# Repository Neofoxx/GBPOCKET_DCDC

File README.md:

# Alternative DCDC converter board for the Gameboy Pocket

This board provides higher efficiency than the stock converter, alowwing you to use rechargeable bateries to their full potential.

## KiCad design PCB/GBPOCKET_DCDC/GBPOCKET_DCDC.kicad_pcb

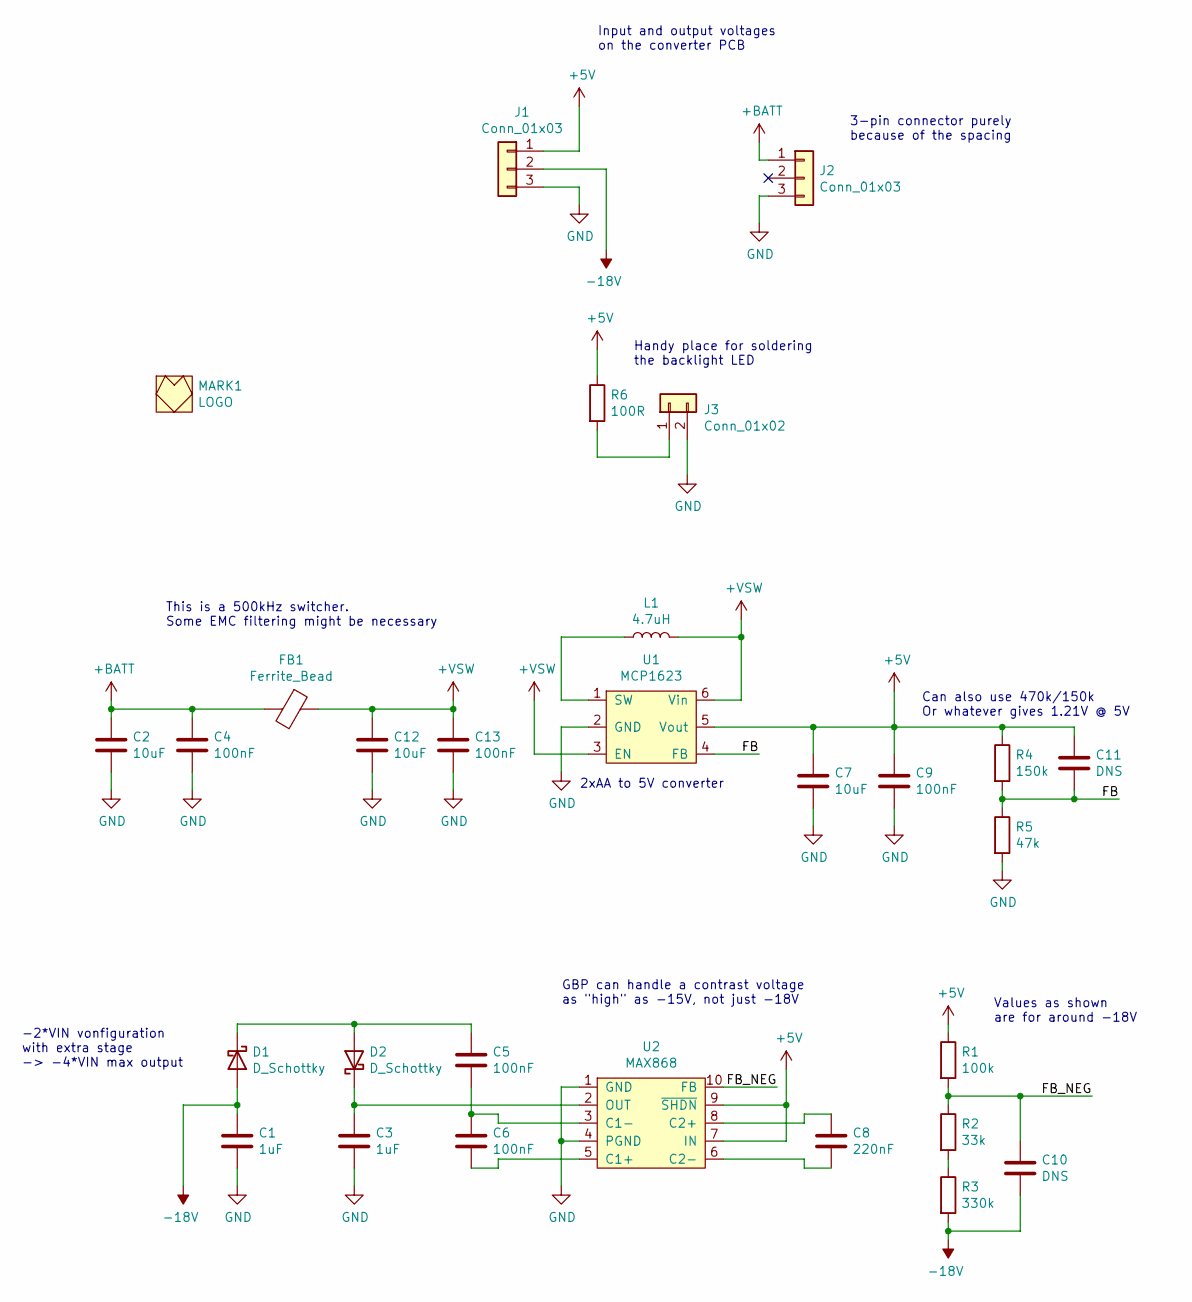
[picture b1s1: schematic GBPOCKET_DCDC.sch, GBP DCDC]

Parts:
C1, C3: 1uF; C_0603_1608Metric_Pad1.08x0.95mm_HandSolder
C2, C7, C12: 10uF; C_0805_2012Metric_Pad1.18x1.45mm_HandSolder
C4, C5, C6, C9, C13: 100nF; C_0603_1608Metric_Pad1.08x0.95mm_HandSolder
C8: 220nF; C_0603_1608Metric_Pad1.08x0.95mm_HandSolder
C10, C11: DNS; C_0603_1608Metric_Pad1.08x0.95mm_HandSolder
D1, D2: D_Schottky; D_SOD-323_HandSoldering
FB1: Ferrite_Bead; L_0805_2012Metric_Pad1.15x1.40mm_HandSolder
J1, J2: Conn_01x03; PinHeader_1x03_P2.54mm_Vertical
J3: Conn_01x02; PinHeader_1x02_P2.54mm_Vertical
L1: 4.7uH; SMNR4018_(1616FPS)
MARK1: LOGO; FOX_LOGO_SILK
R1: 100k; R_0603_1608Metric_Pad0.98x0.95mm_HandSolder
R2: 33k; R_0603_1608Metric_Pad0.98x0.95mm_HandSolder
R3: 330k; R_0603_1608Metric_Pad0.98x0.95mm_HandSolder
R4: 150k; R_0603_1608Metric_Pad0.98x0.95mm_HandSolder
R5: 47k; R_0603_1608Metric_Pad0.98x0.95mm_HandSolder
R6: 100R; R_0603_1608Metric_Pad0.98x0.95mm_HandSolder
U1: MCP1623; SOT-23-6_Handsoldering
U2: MAX868; MSOP-10_3x3mm_P0.5mm

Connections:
+5V: C7.1, C9.1, C11.1, J1.1, R1.1, R4.1, R6.1, U1.5 (Vout), U2.7 (IN), U2.9 (~SHDN~)
+BATT: C2.1, C4.1, FB1.2, J2.1
+VSW: C12.1, C13.1, FB1.1, L1.2, U1.3 (EN), U1.6 (Vin)
-18V: C1.1, C10.2, D1.2 (A), J1.2, R3.2
/FB: C11.2, R4.2, R5.1, U1.4 (FB)
/FB_NEG: C10.1, R1.2, R2.1, U2.10 (FB)
GND: C1.2, C2.2, C3.2, C4.2, C7.2, C9.2, C12.2, C13.2, J1.3, J2.3, J3.2, R5.2, U1.2 (GND), U2.1 (GND), U2.4 (PGND)
unnamed: C3.1, D2.1 (K), U2.2 (OUT)
unnamed: C5.1, D1.1 (K), D2.2 (A)
unnamed: C5.2, C6.1, U2.3 (C1-)
unnamed: C6.2, U2.5 (C1+)
unnamed: C8.1, U2.8 (C2+)
unnamed: C8.2, U2.6 (C2-)
unnamed: J3.1, R6.2
unnamed: L1.1, U1.1 (SW)
unnamed: R2.2, R3.1

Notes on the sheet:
Input and output voltages on the converter PCB
3-pin connector purely because of the spacing
This is a 500kHz switcher. Some EMC filtering might be necessary
2xAA to 5V converter
-2*VIN vonfiguration with extra stage -> -4*VIN max output
Values as shown are for around -18V
GBP can handle a contrast voltage as "high" as -15V, not just -18V
Can also use 470k/150k Or whatever gives 1.21V @ 5V
Handy place for soldering the backlight LED

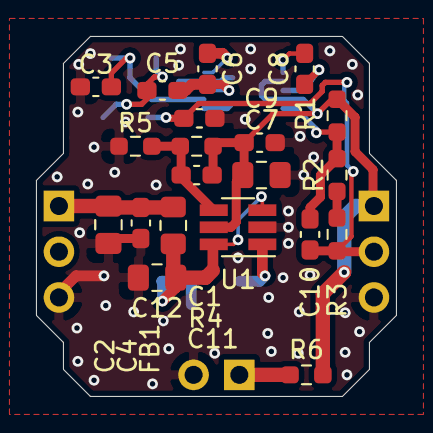
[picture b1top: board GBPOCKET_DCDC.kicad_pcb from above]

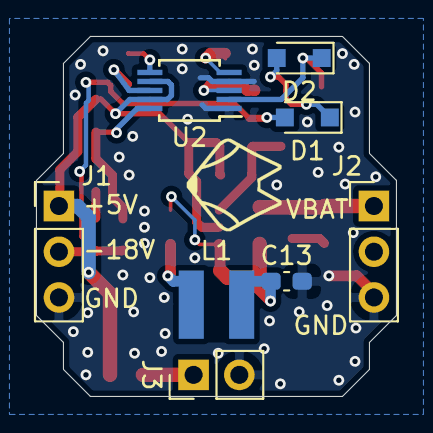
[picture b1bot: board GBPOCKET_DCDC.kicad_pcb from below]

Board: 2 copper layers, 20.0 x 20.0 mm, 29 parts (9 on the bottom side), 16 nets.

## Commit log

2021-11-13 Init repo and add README
2021-11-13 Add .gitignore
2021-11-13 Add schematic portion
2021-11-14 Updated schematic a bit Added header for LED Finished PCB (quick'n'dirty, bit it'll do) Exported gerbers for production
